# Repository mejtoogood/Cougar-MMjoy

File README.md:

# Cougar-MMjoy
Refurbishing and modernising a [Thrustmaster Cougar HOTAS](http://cougar.flyfoxy.com/) using the excellent [MMjoy project](github.com/MMjoy/mmjoy_en) and [TLE5010 Magnetoresistive Sensors](https://github.com/mejtoogood/TLE5010)

<br />This work is licensed under a <a rel="license" href="http://creativecommons.org/licenses/by-nc-sa/4.0/">Creative Commons Attribution-NonCommercial-ShareAlike 4.0 International License</a>.

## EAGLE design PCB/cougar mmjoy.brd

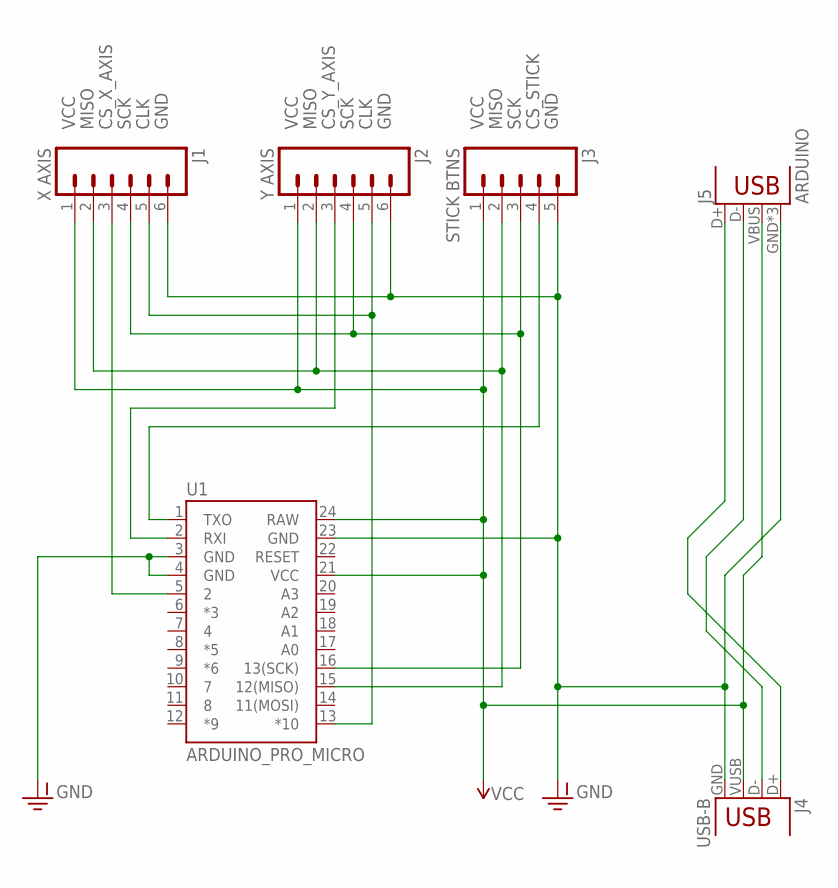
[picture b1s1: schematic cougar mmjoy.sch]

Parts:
J1: X AXIS; MOLEX-1X6_LOCK
J2: Y AXIS; MOLEX-1X6_LOCK
J3: STICK BTNS; 1X05_LOCK
J4: USB-B; USB-B-SMT
J5: ARDUINO; USB-MICROB
U1: ARDUINO_PRO_MICRO

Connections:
CLK: J1.5, J2.5, U1.13 (*10)
CS_STICK: J3.4, U1.1 (TXO)
CS_X_AXIS: J1.3, U1.5 (2)
CS_Y_AXIS: J2.3, U1.2 (RXI)
GND: J1.6, J2.6, J3.5, J4.GND, J5.GND, J5.MT1 (GND), J5.MT2 (GND), U1.3 (GND), U1.4 (GND), U1.23 (GND)
MISO: J1.2, J2.2, J3.2, U1.15 (12(MISO))
unnamed: J4.D-, J5.D-
unnamed: J4.D+, J5.D+
SCK: J1.4, J2.4, J3.3, U1.16 (13(SCK))
VCC: J1.1, J2.1, J3.1, J4.VUSB (VBUS), J5.VBUS, U1.21 (VCC), U1.24 (RAW)

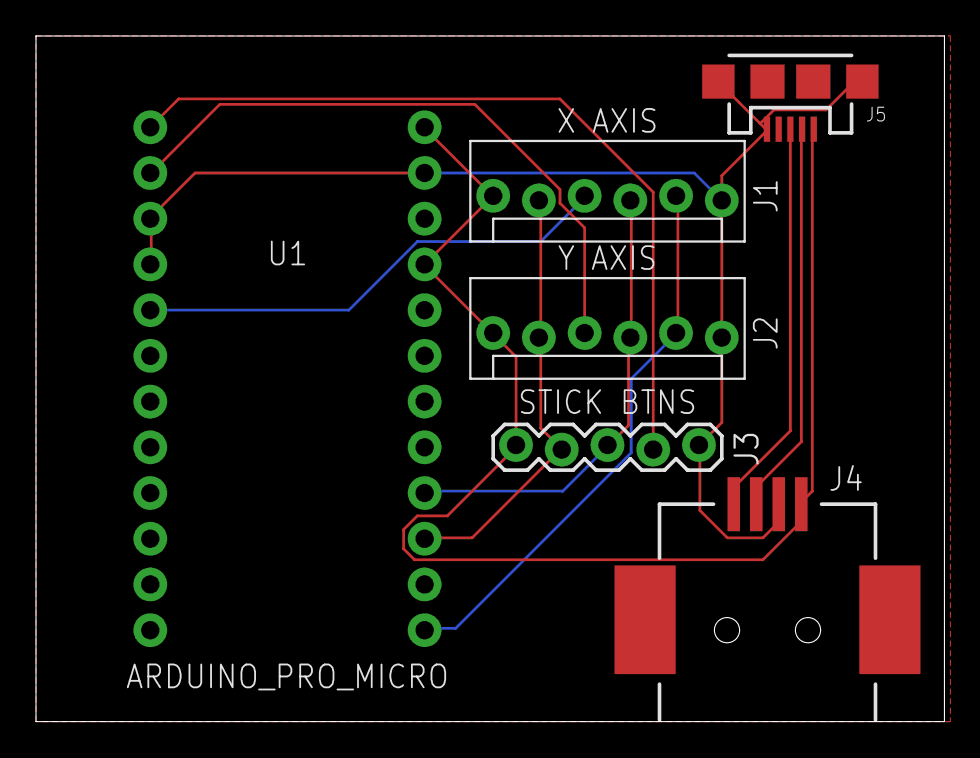
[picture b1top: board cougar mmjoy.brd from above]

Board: 2 copper layers, 50.5 x 38.1 mm, 6 parts (0 on the bottom side), 10 nets.

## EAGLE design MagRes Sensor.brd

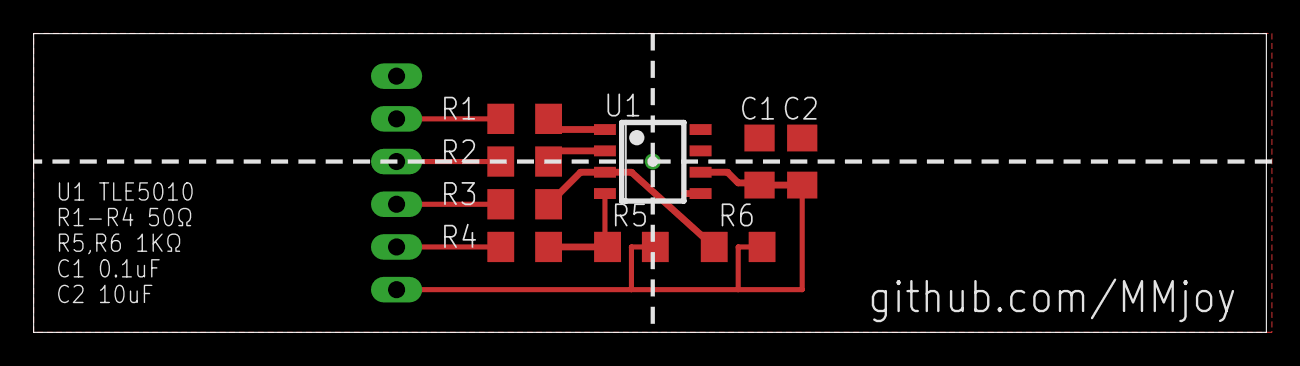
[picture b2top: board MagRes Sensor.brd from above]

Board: 2 copper layers, 73.3 x 17.8 mm, 10 parts (1 on the bottom side), 10 nets.

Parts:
C1: 0.1uF; C1206
C2: 10uF; C1206
J1: MA06-1
R1, R2, R3, R4: 50; R1206
R5, R6: 1K; R1206
U1: TLE5010; PG-DSO-8

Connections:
GND: C1.1, C2.1, J1.6, U1.5, U1.7, U1.8
unnamed: R1.2, U1.1
unnamed: R2.2, U1.2
unnamed: J1.5, R1.1
unnamed: J1.4, R2.1
unnamed: J1.3, R3.1
unnamed: R3.2, R6.1, U1.3
unnamed: R4.2, R5.1, U1.4
unnamed: J1.2, R4.1
VCC: C1.2, C2.2, J1.1, R5.2, R6.2, U1.6

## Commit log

2016-05-16 Open repo
    Start project
2016-05-16 First Revision
    Commit of First Revision based on PCB for TLE5010 from
    github.com/MMJoy/mmjoy_en
2016-05-16 Directory Structure
    Housekeeping
2016-05-16 Adjust Silkscreen
    Changed minimum line width to 5 mils based on OSH Park docs
2016-05-17 Housekeeping
    Made public, fix dir structure, updated readme
2016-05-17 Updated SketchUp models
    Created detailed SketchUp models, concept graphic
2016-05-17 Updated names, added pics
    Changed dir names, removed eagleup leftovers, added pics from sketchup

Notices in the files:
PCB/cougar mmjoy.brd:
CC BY NC SA
parts and their libraries:
SparkFun-Connectors: Licensing: Creative Commons ShareAlike 4.0 International - https://creativecommons.org/licenses/by-sa/4.0
